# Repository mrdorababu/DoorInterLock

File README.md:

# DoorInterLock
Controls the access  through three doors and these doors are interlinked , opening any one door will lock the other doors. Emergency exits are provided for oprtional.

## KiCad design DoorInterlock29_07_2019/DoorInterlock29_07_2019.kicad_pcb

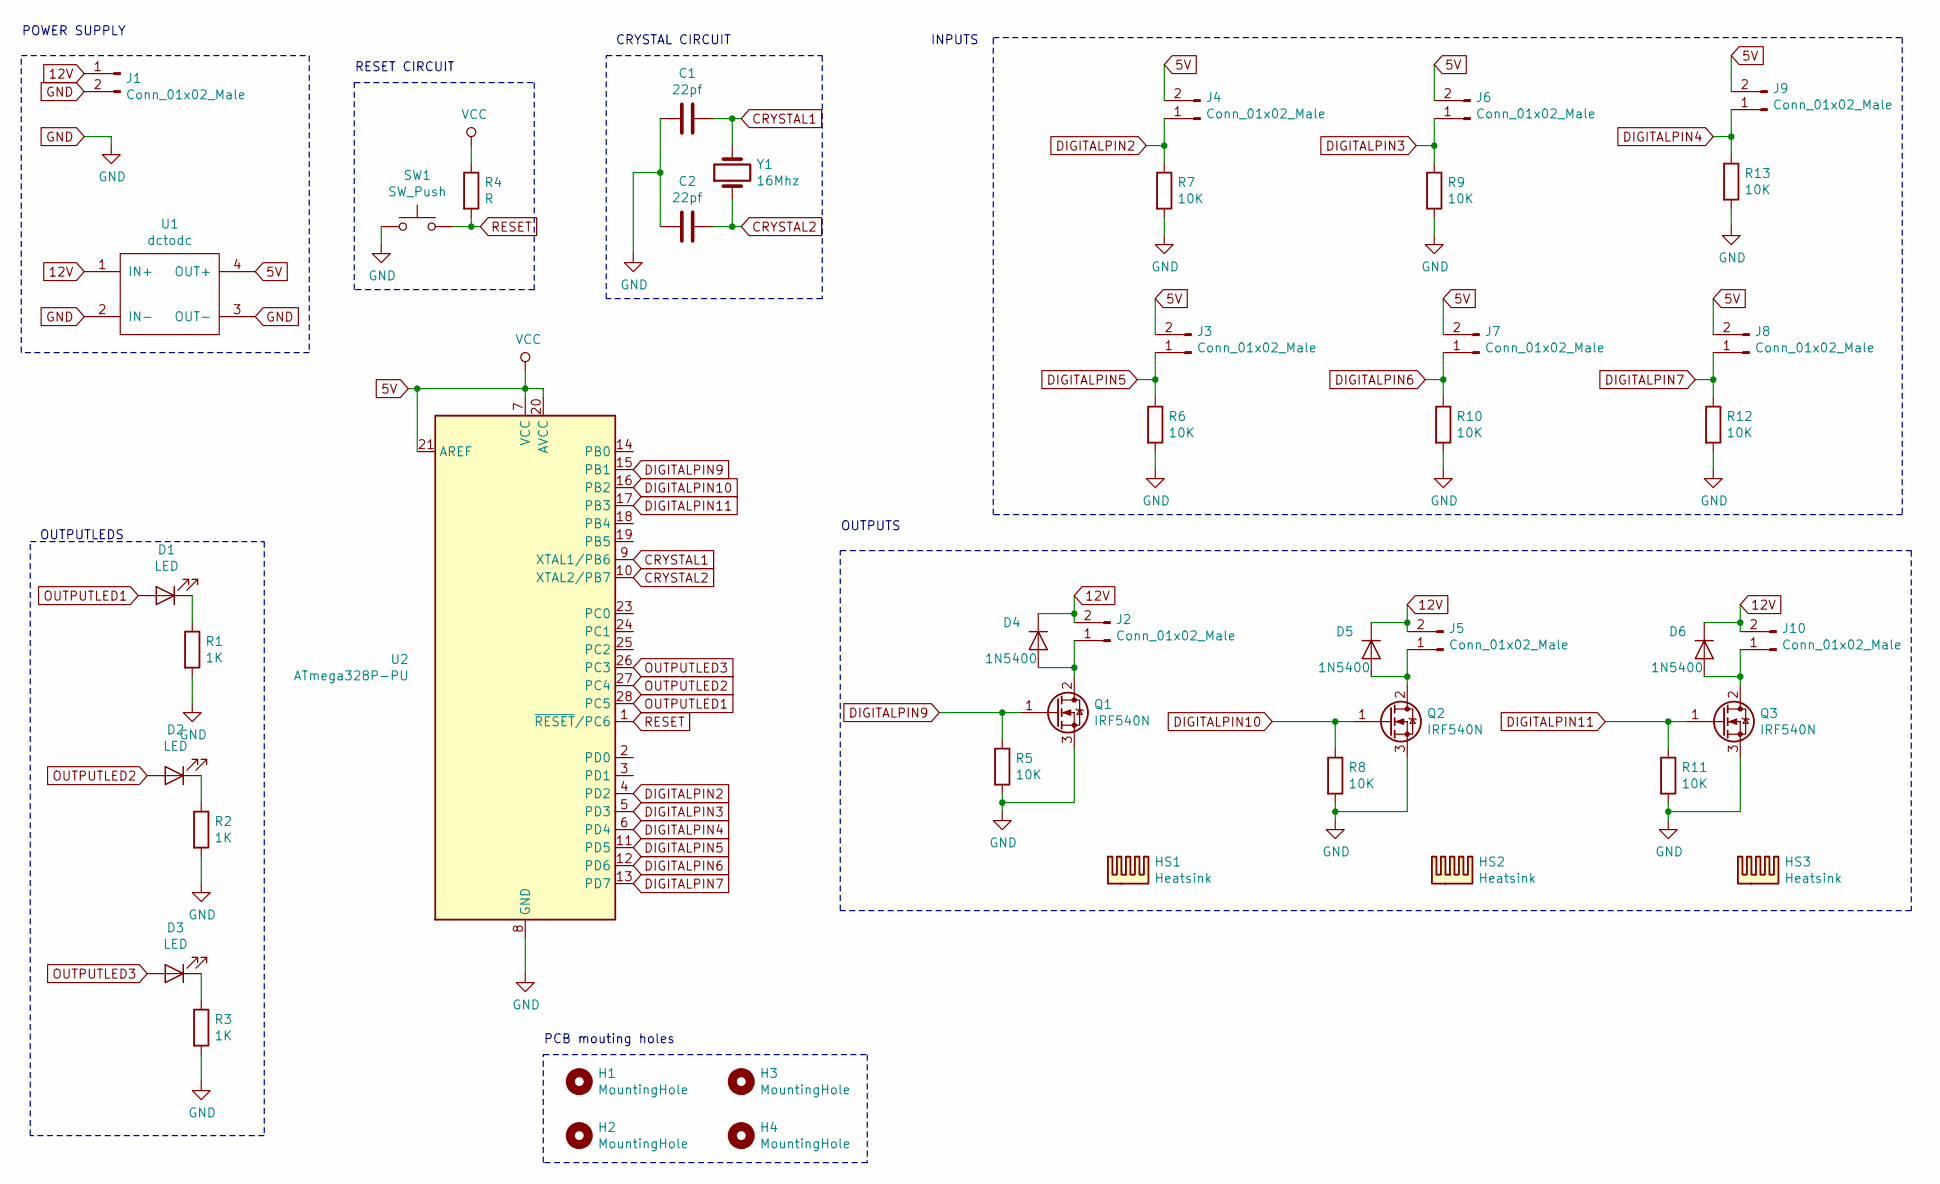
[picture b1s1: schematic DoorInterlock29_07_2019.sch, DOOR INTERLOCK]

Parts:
C1, C2: 22pf; C_Disc_D3.8mm_W2.6mm_P2.50mm
D1, D2, D3: LED; LED_D5.0mm
D4, D5, D6: 1N5400; D_DO-27_P5.08mm_Vertical_KathodeUp
H1, H2, H3, H4: MountingHole; MountingHole_4.3mm_M4
HS1, HS2, HS3: Heatsink; Heatsink_Aavid-TV5G_TO220_Horizontal
J1, J2, J5, J10: Conn_01x02_Male; TerminalBlock_bornier-2_P5.08mm
J3, J4, J6, J7, J8, J9: Conn_01x02_Male; Molex_KK-6410-02_02x2.54mm_Straight
Q1, Q2, Q3: IRF540N; TO-220-3_Vertical
R1, R2, R3: 1K; R_Axial_DIN0309_L9.0mm_D3.2mm_P12.70mm_Horizontal
R4: R; R_Axial_DIN0309_L9.0mm_D3.2mm_P12.70mm_Horizontal
R5, R6, R7, R8, R9, R10, R11, R12, R13: 10K; R_Axial_DIN0309_L9.0mm_D3.2mm_P12.70mm_Horizontal
SW1: SW_Push; SW_PUSH_6mm_h4.3mm
U1: dctodc; DCtoDCconverter
U2: ATmega328P-PU; DIP-28_W7.62mm_Socket_LongPads
Y1: 16Mhz; Crystal_HC50_Vertical

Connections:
5V: J3.2, J4.2, J6.2, J7.2, J8.2, J9.2, R4.1, U1.4 (OUT+), U2.7 (VCC), U2.20 (AVCC), U2.21 (AREF)
12V: D4.1 (K), D5.1 (K), D6.1 (K), J1.1, J2.2, J5.2, J10.2, U1.1 (IN+)
CRYSTAL1: C1.2, U2.9 (XTAL1/PB6), Y1.2
CRYSTAL2: C2.1, U2.10 (XTAL2/PB7), Y1.1
DIGITALPIN2: J4.1, R7.1, U2.4 (PD2)
DIGITALPIN3: J6.1, R9.1, U2.5 (PD3)
DIGITALPIN4: J9.1, R13.1, U2.6 (PD4)
DIGITALPIN5: J3.1, R6.1, U2.11 (PD5)
DIGITALPIN6: J7.1, R10.1, U2.12 (PD6)
DIGITALPIN7: J8.1, R12.1, U2.13 (PD7)
DIGITALPIN9: Q1.1 (G), R5.1, U2.15 (PB1)
DIGITALPIN10: Q2.1 (G), R8.1, U2.16 (PB2)
DIGITALPIN11: Q3.1 (G), R11.1, U2.17 (PB3)
GND: C1.1, C2.2, J1.2, Q1.3 (S), Q2.3 (S), Q3.3 (S), R1.2, R2.2, R3.2, R5.2, R6.2, R7.2, R8.2, R9.2, R10.2, R11.2, R12.2, R13.2, SW1.1, U1.2 (IN-), U1.3 (OUT-), U2.8 (GND), U2.22 (GND)
unnamed: D1.1 (K), R1.1
unnamed: D2.1 (K), R2.1
unnamed: D3.1 (K), R3.1
unnamed: D4.2 (A), J2.1, Q1.2 (D)
unnamed: D5.2 (A), J5.1, Q2.2 (D)
unnamed: D6.2 (A), J10.1, Q3.2 (D)
OUTPUTLED1: D1.2 (A), U2.28 (PC5)
OUTPUTLED2: D2.2 (A), U2.27 (PC4)
OUTPUTLED3: D3.2 (A), U2.26 (PC3)
RESET: R4.2, SW1.2, U2.1 (~RESET~/PC6)

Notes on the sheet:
RESET CIRCUIT
CRYSTAL CIRCUIT
POWER SUPPLY
INPUTS
OUTPUTS
OUTPUTLEDS
PCB mouting holes

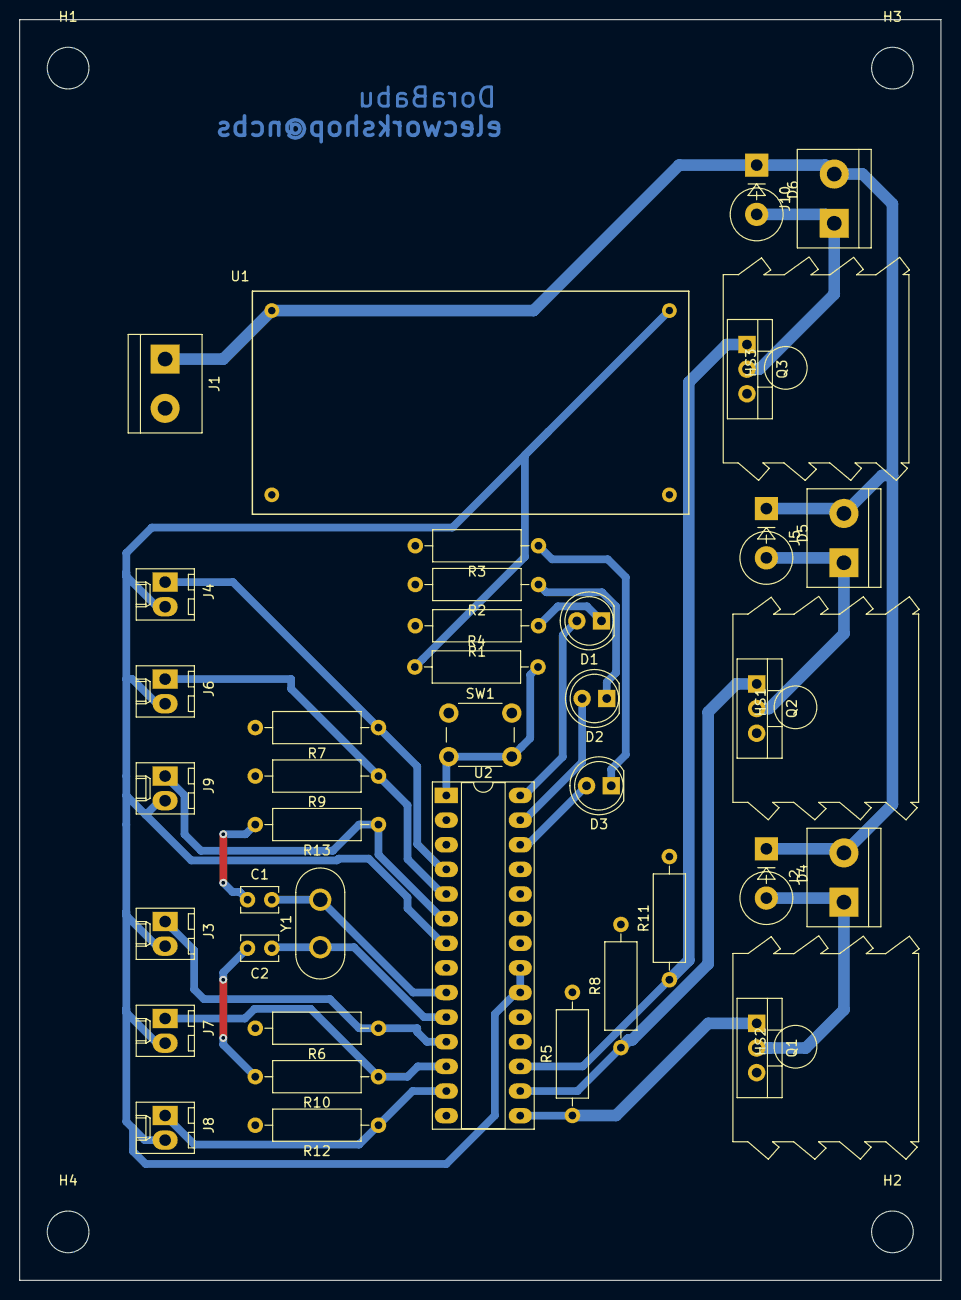
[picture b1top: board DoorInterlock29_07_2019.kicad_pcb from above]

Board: 2 copper layers, 95.0 x 130.0 mm, 45 parts (0 on the bottom side), 24 nets.

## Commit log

2019-08-01 Two doorInterlock added
